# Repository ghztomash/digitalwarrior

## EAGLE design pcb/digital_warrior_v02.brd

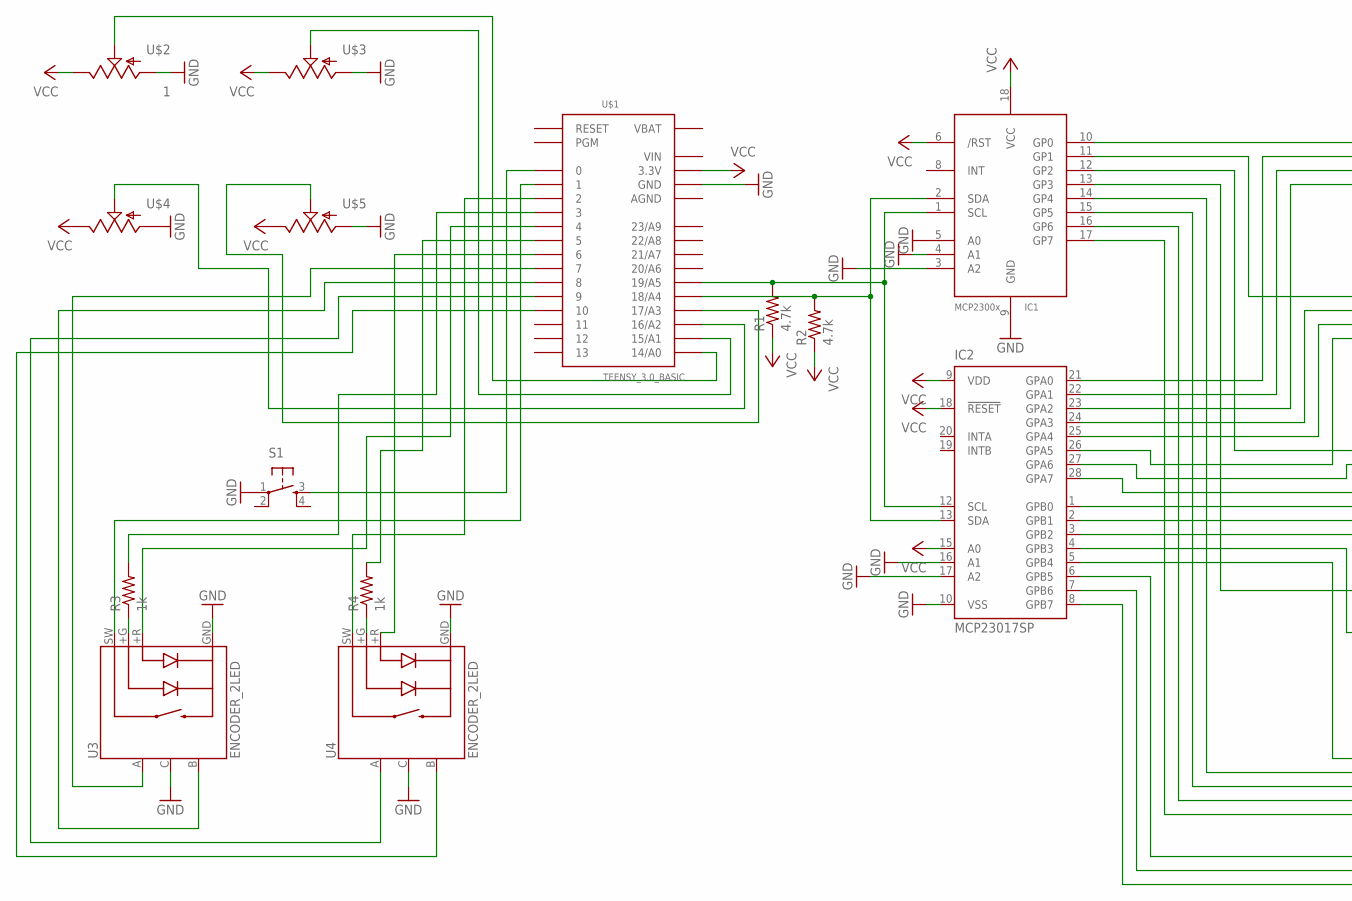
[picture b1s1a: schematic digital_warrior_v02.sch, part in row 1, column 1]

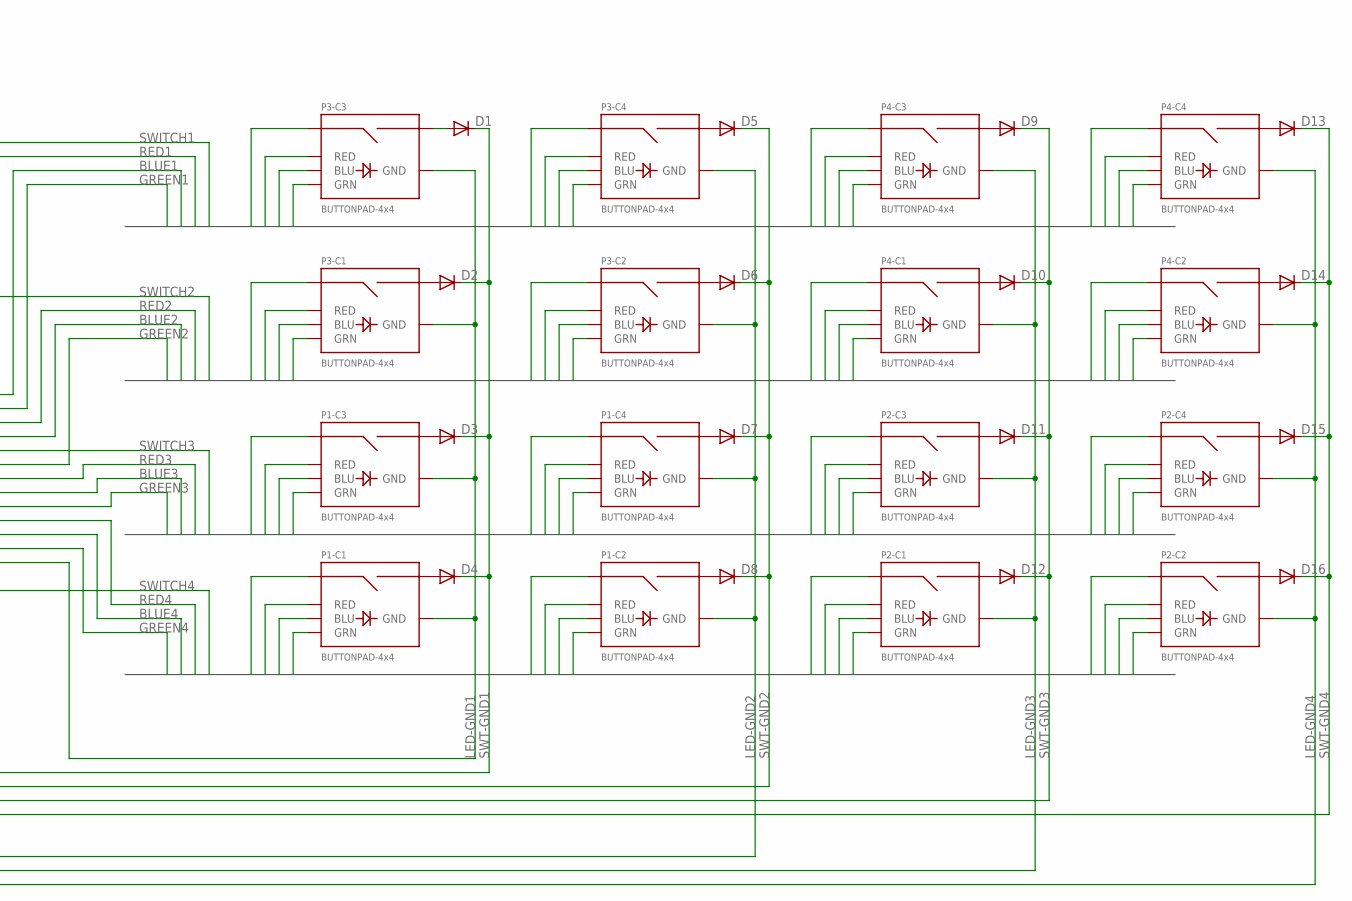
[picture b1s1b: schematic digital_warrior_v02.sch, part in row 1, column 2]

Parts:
D1, D2, D3, D4, D5, D6, D7, D8, D9, D10, D11, D12, D13, D14, D15, D16: DIODE-1N4148; DOIDE-1N4148
IC1: MCP2300X/P; DIL18
IC2: MCP23017SP; DIL28-3
P1, P2, P3, P4: BUTTONPAD-4x4; BUTTONPAD-2X2
R1, R2: 4.7k; AXIAL-0.4
R3, R4: 1k; AXIAL-0.4
S1: TAC_SWITCHPTH; TACTILE-PTH
U3, U4: ENCODER_2LED; ENCODER_LED_2
U$1: TEENSY_3.0_BASIC
U$2: 1; ALPS_POT
U$3, U$4, U$5: POT; ALPS_POT

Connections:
AGND: U$1.AGND
BLUE1: IC2.22 (GPA1), P3.BLU3 (BLU), P3.BLU4 (BLU), P4.BLU3 (BLU), P4.BLU4 (BLU)
BLUE2: IC2.25 (GPA4), P3.BLU1 (BLU), P3.BLU2 (BLU), P4.BLU1 (BLU), P4.BLU2 (BLU)
BLUE3: IC2.28 (GPA7), P1.BLU3 (BLU), P1.BLU4 (BLU), P2.BLU3 (BLU), P2.BLU4 (BLU)
BLUE4: IC2.3 (GPB2), P1.BLU1 (BLU), P1.BLU2 (BLU), P2.BLU1 (BLU), P2.BLU2 (BLU)
GND: IC1.3 (A2), IC1.4 (A1), IC1.5 (A0), IC1.9 (GND), IC2.10 (VSS), IC2.16 (A1), IC2.17 (A2), S1.1, U3.C, U3.GND (-), U4.C, U4.GND (-), U$1.GND, U$1.GND1 (GND), U$2.P$3 (A), U$3.P$3 (A), U$4.P$3 (A), U$5.P$3 (A)
GREEN1: IC2.23 (GPA2), P3.GRN3 (GRN), P3.GRN4 (GRN), P4.GRN3 (GRN), P4.GRN4 (GRN)
GREEN2: IC2.26 (GPA5), P3.GRN1 (GRN), P3.GRN2 (GRN), P4.GRN1 (GRN), P4.GRN2 (GRN)
GREEN3: IC2.1 (GPB0), P1.GRN3 (GRN), P1.GRN4 (GRN), P2.GRN3 (GRN), P2.GRN4 (GRN)
GREEN4: IC2.4 (GPB3), P1.GRN1 (GRN), P1.GRN2 (GRN), P2.GRN1 (GRN), P2.GRN2 (GRN)
LED-GND1: IC2.5 (GPB4), P1.GND1 (GND), P1.GND3 (GND), P3.GND1 (GND), P3.GND3 (GND)
LED-GND2: IC2.6 (GPB5), P1.GND2 (GND), P1.GND4 (GND), P3.GND2 (GND), P3.GND4 (GND)
LED-GND3: IC2.7 (GPB6), P2.GND1 (GND), P2.GND3 (GND), P4.GND1 (GND), P4.GND3 (GND)
LED-GND4: IC2.8 (GPB7), P2.GND2 (GND), P2.GND4 (GND), P4.GND2 (GND), P4.GND4 (GND)
unnamed: D1.P$1 (A), P3.SIG6 (SIG2)
unnamed: D2.P$1 (A), P3.SIG2
unnamed: D3.P$1 (A), P1.SIG6 (SIG2)
unnamed: D4.P$1 (A), P1.SIG2
unnamed: D5.P$1 (A), P3.SIG8 (SIG2)
unnamed: D6.P$1 (A), P3.SIG4 (SIG2)
unnamed: D7.P$1 (A), P1.SIG8 (SIG2)
unnamed: D8.P$1 (A), P1.SIG4 (SIG2)
unnamed: D9.P$1 (A), P4.SIG6 (SIG2)
unnamed: D10.P$1 (A), P4.SIG2
unnamed: D11.P$1 (A), P2.SIG6 (SIG2)
unnamed: D12.P$1 (A), P2.SIG2
unnamed: D13.P$1 (A), P4.SIG8 (SIG2)
unnamed: D14.P$1 (A), P4.SIG4 (SIG2)
unnamed: D15.P$1 (A), P2.SIG8 (SIG2)
unnamed: D16.P$1 (A), P2.SIG4 (SIG2)
unnamed: IC1.1 (SCL), IC2.12 (SCL), R1.P$2 (2), U$1.19/A5
unnamed: IC1.2 (SDA), IC2.13 (SDA), R2.P$2 (2), U$1.18/A4
unnamed: U$1.14/A0, U$2.P$2 (S)
unnamed: U$1.15/A1, U$3.P$2 (S)
unnamed: U$1.16/A2, U$4.P$2 (S)
unnamed: U$1.17/A3, U$5.P$2 (S)
unnamed: S1.3, U$1.0
unnamed: U3.SW, U$1.1
unnamed: U4.SW, U$1.2
unnamed: R3.P$2 (2), U$1.3
unnamed: U3.+R, U$1.4
unnamed: R3.P$1 (1), U3.+G
unnamed: R4.P$1 (1), U4.+G
unnamed: R4.P$2 (2), U$1.5
unnamed: U4.+R, U$1.6
unnamed: U3.A, U$1.7
unnamed: U3.B, U$1.8
unnamed: U4.A, U$1.9
unnamed: U4.B, U$1.10
RED1: IC2.21 (GPA0), P3.RED3 (RED), P3.RED4 (RED), P4.RED3 (RED), P4.RED4 (RED)
RED2: IC2.24 (GPA3), P3.RED1 (RED), P3.RED2 (RED), P4.RED1 (RED), P4.RED2 (RED)
RED3: IC2.27 (GPA6), P1.RED3 (RED), P1.RED4 (RED), P2.RED3 (RED), P2.RED4 (RED)
RED4: IC2.2 (GPB1), P1.RED1 (RED), P1.RED2 (RED), P2.RED1 (RED), P2.RED2 (RED)
SWITCH1: IC1.10 (GP0), P3.SIG5 (SIG1), P3.SIG7 (SIG1), P4.SIG5 (SIG1), P4.SIG7 (SIG1)
SWITCH2: IC1.11 (GP1), P3.SIG1, P3.SIG3 (SIG1), P4.SIG1, P4.SIG3 (SIG1)
SWITCH3: IC1.12 (GP2), P1.SIG5 (SIG1), P1.SIG7 (SIG1), P2.SIG5 (SIG1), P2.SIG7 (SIG1)
SWITCH4: IC1.13 (GP3), P1.SIG1, P1.SIG3 (SIG1), P2.SIG1, P2.SIG3 (SIG1)
SWT-GND1: D1.P$2 (C), D2.P$2 (C), D3.P$2 (C), D4.P$2 (C), IC1.14 (GP4)
SWT-GND2: D5.P$2 (C), D6.P$2 (C), D7.P$2 (C), D8.P$2 (C), IC1.15 (GP5)
SWT-GND3: D9.P$2 (C), D10.P$2 (C), D11.P$2 (C), D12.P$2 (C), IC1.16 (GP6)
SWT-GND4: D13.P$2 (C), D14.P$2 (C), D15.P$2 (C), D16.P$2 (C), IC1.17 (GP7)
VBAT: U$1.VBAT
VCC: IC1.6 (/RST), IC1.18 (VCC), IC2.9 (VDD), IC2.15 (A0), IC2.18 (!RESET), R1.P$1 (1), R2.P$1 (1), U$1.3.3V, U$1.3.3V1 (3.3V), U$2.P$1 (E), U$3.P$1 (E), U$4.P$1 (E), U$5.P$1 (E)
VIN: U$1.VIN

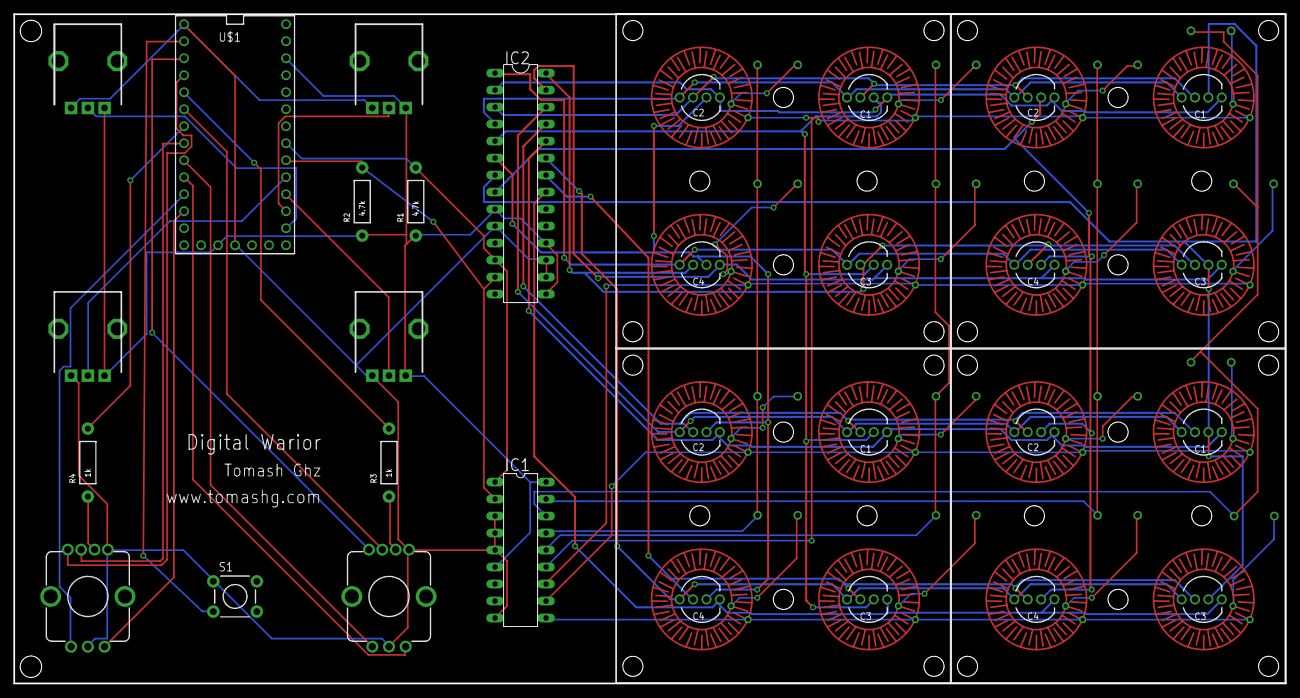
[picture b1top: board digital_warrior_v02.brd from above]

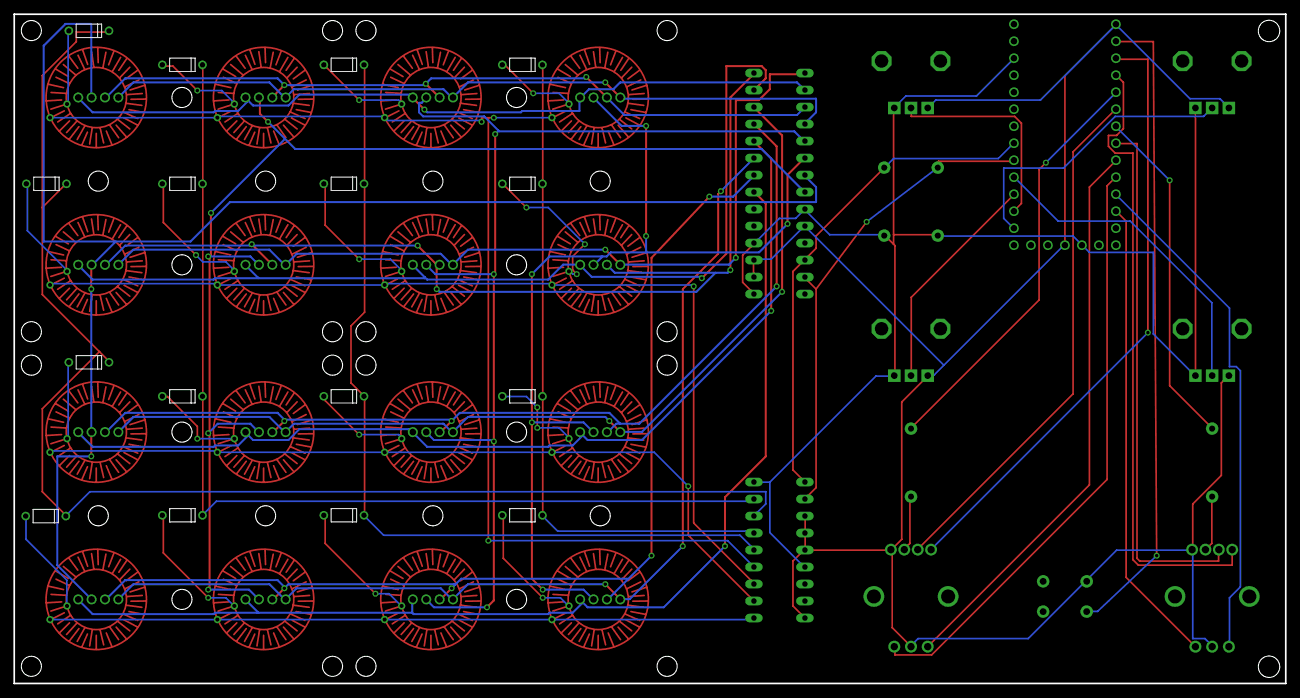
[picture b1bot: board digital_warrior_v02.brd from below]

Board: 2 copper layers, 190.0 x 100.0 mm, 34 parts (20 on the bottom side), 61 nets.

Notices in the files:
parts and their libraries:
SparkFun-Electromechanical: Licensing: CC v3.0 Share-Alike You are welcome to use this library for commercial purposes.
